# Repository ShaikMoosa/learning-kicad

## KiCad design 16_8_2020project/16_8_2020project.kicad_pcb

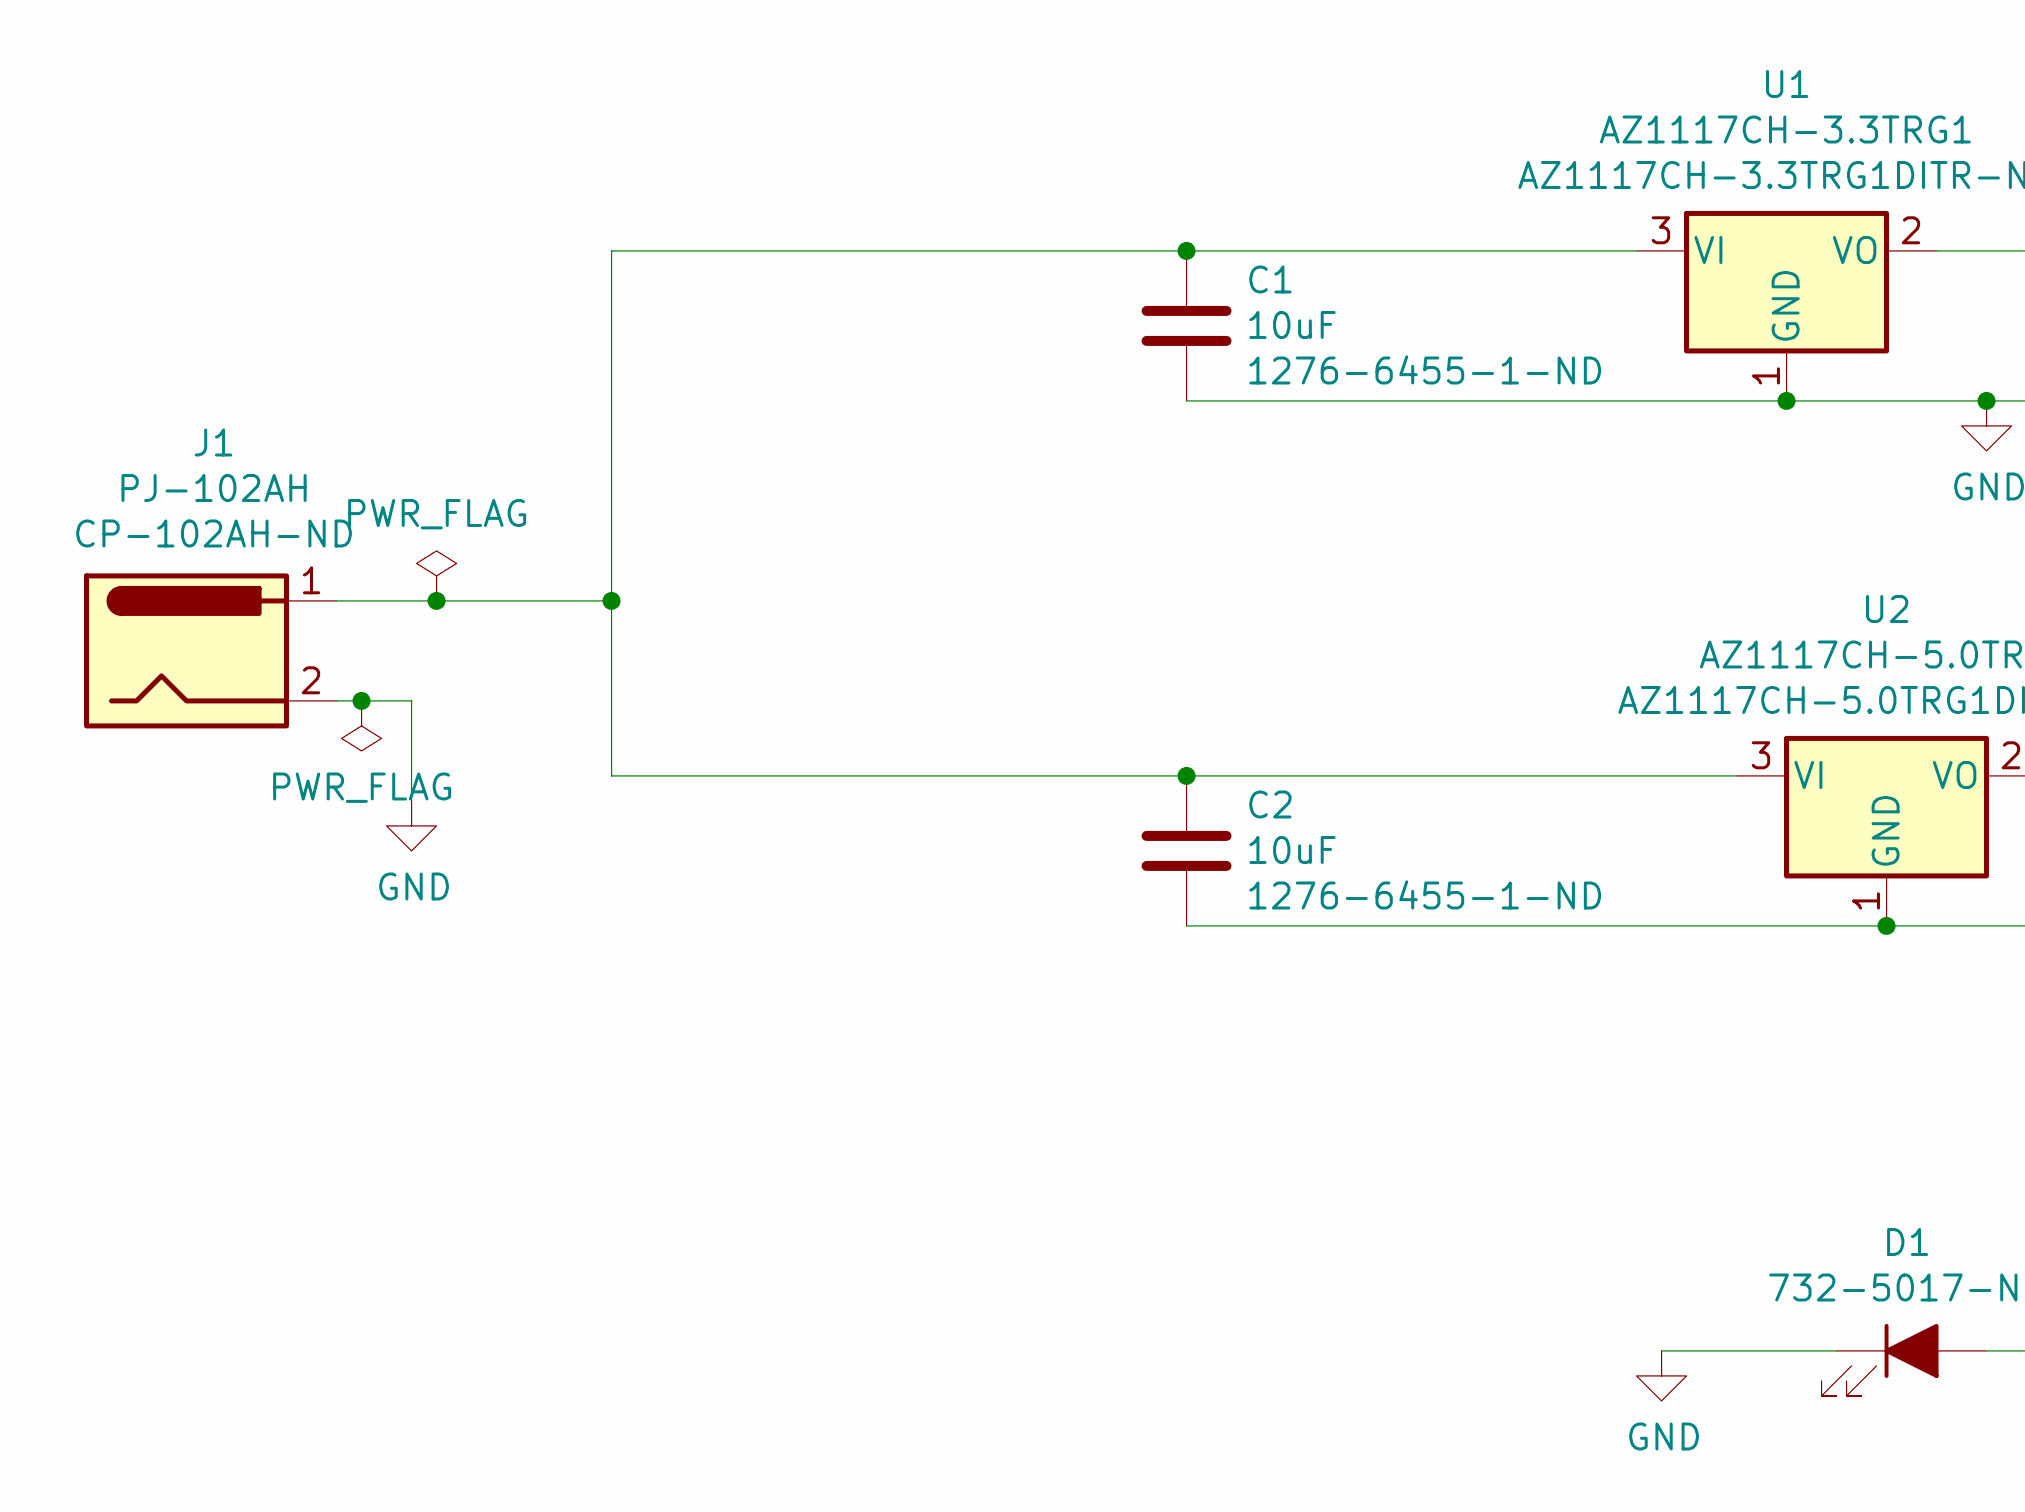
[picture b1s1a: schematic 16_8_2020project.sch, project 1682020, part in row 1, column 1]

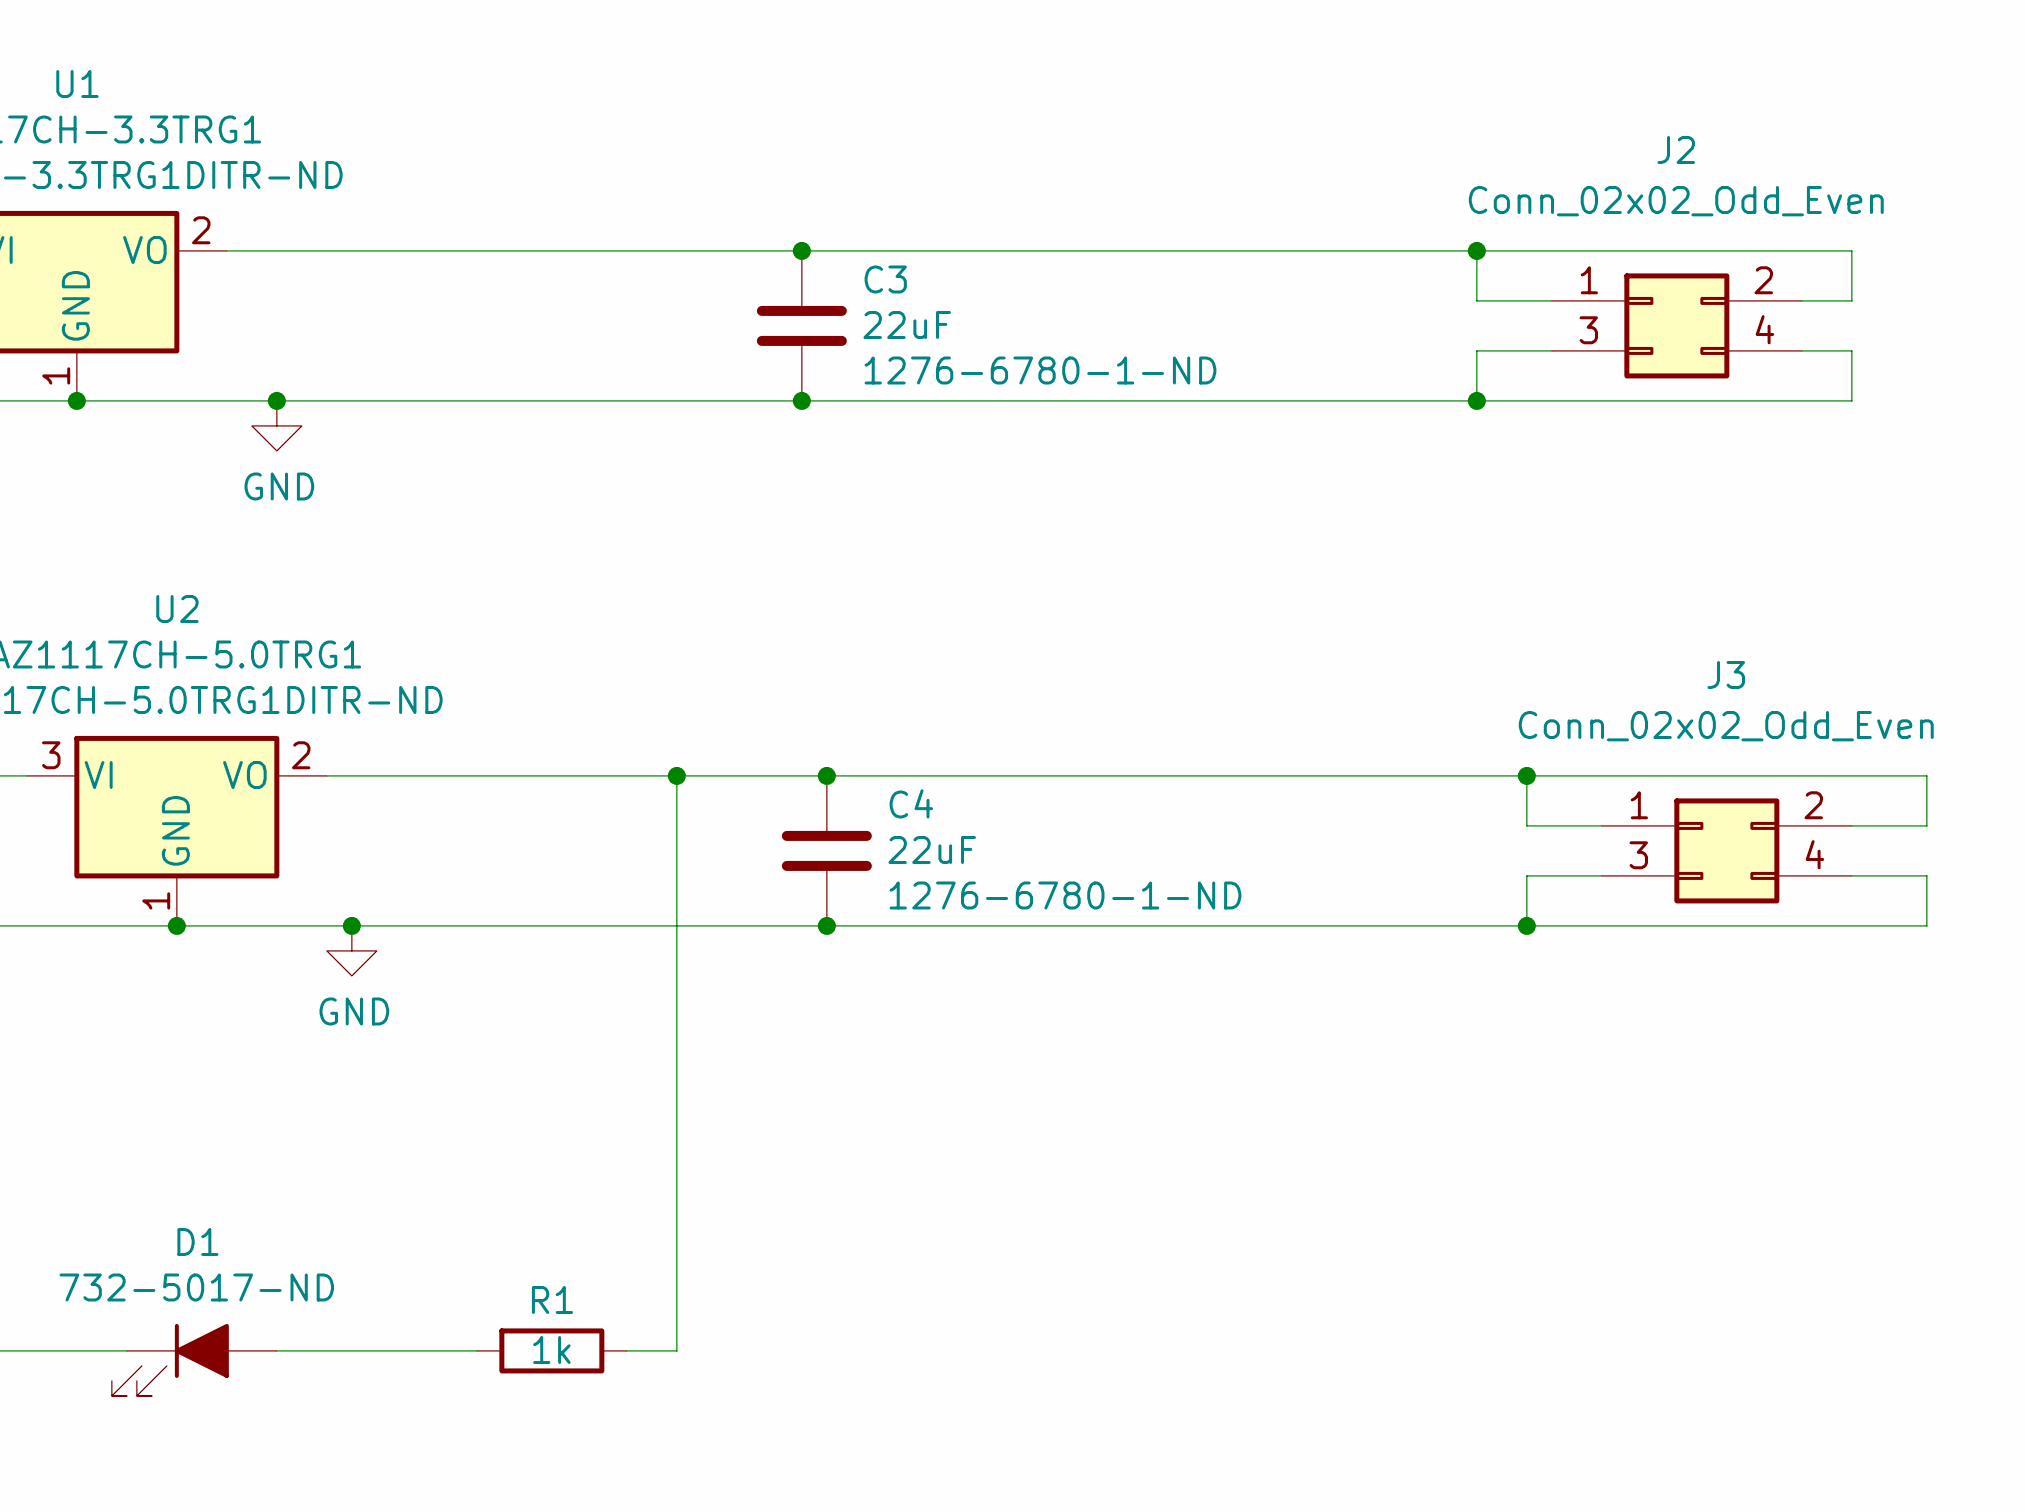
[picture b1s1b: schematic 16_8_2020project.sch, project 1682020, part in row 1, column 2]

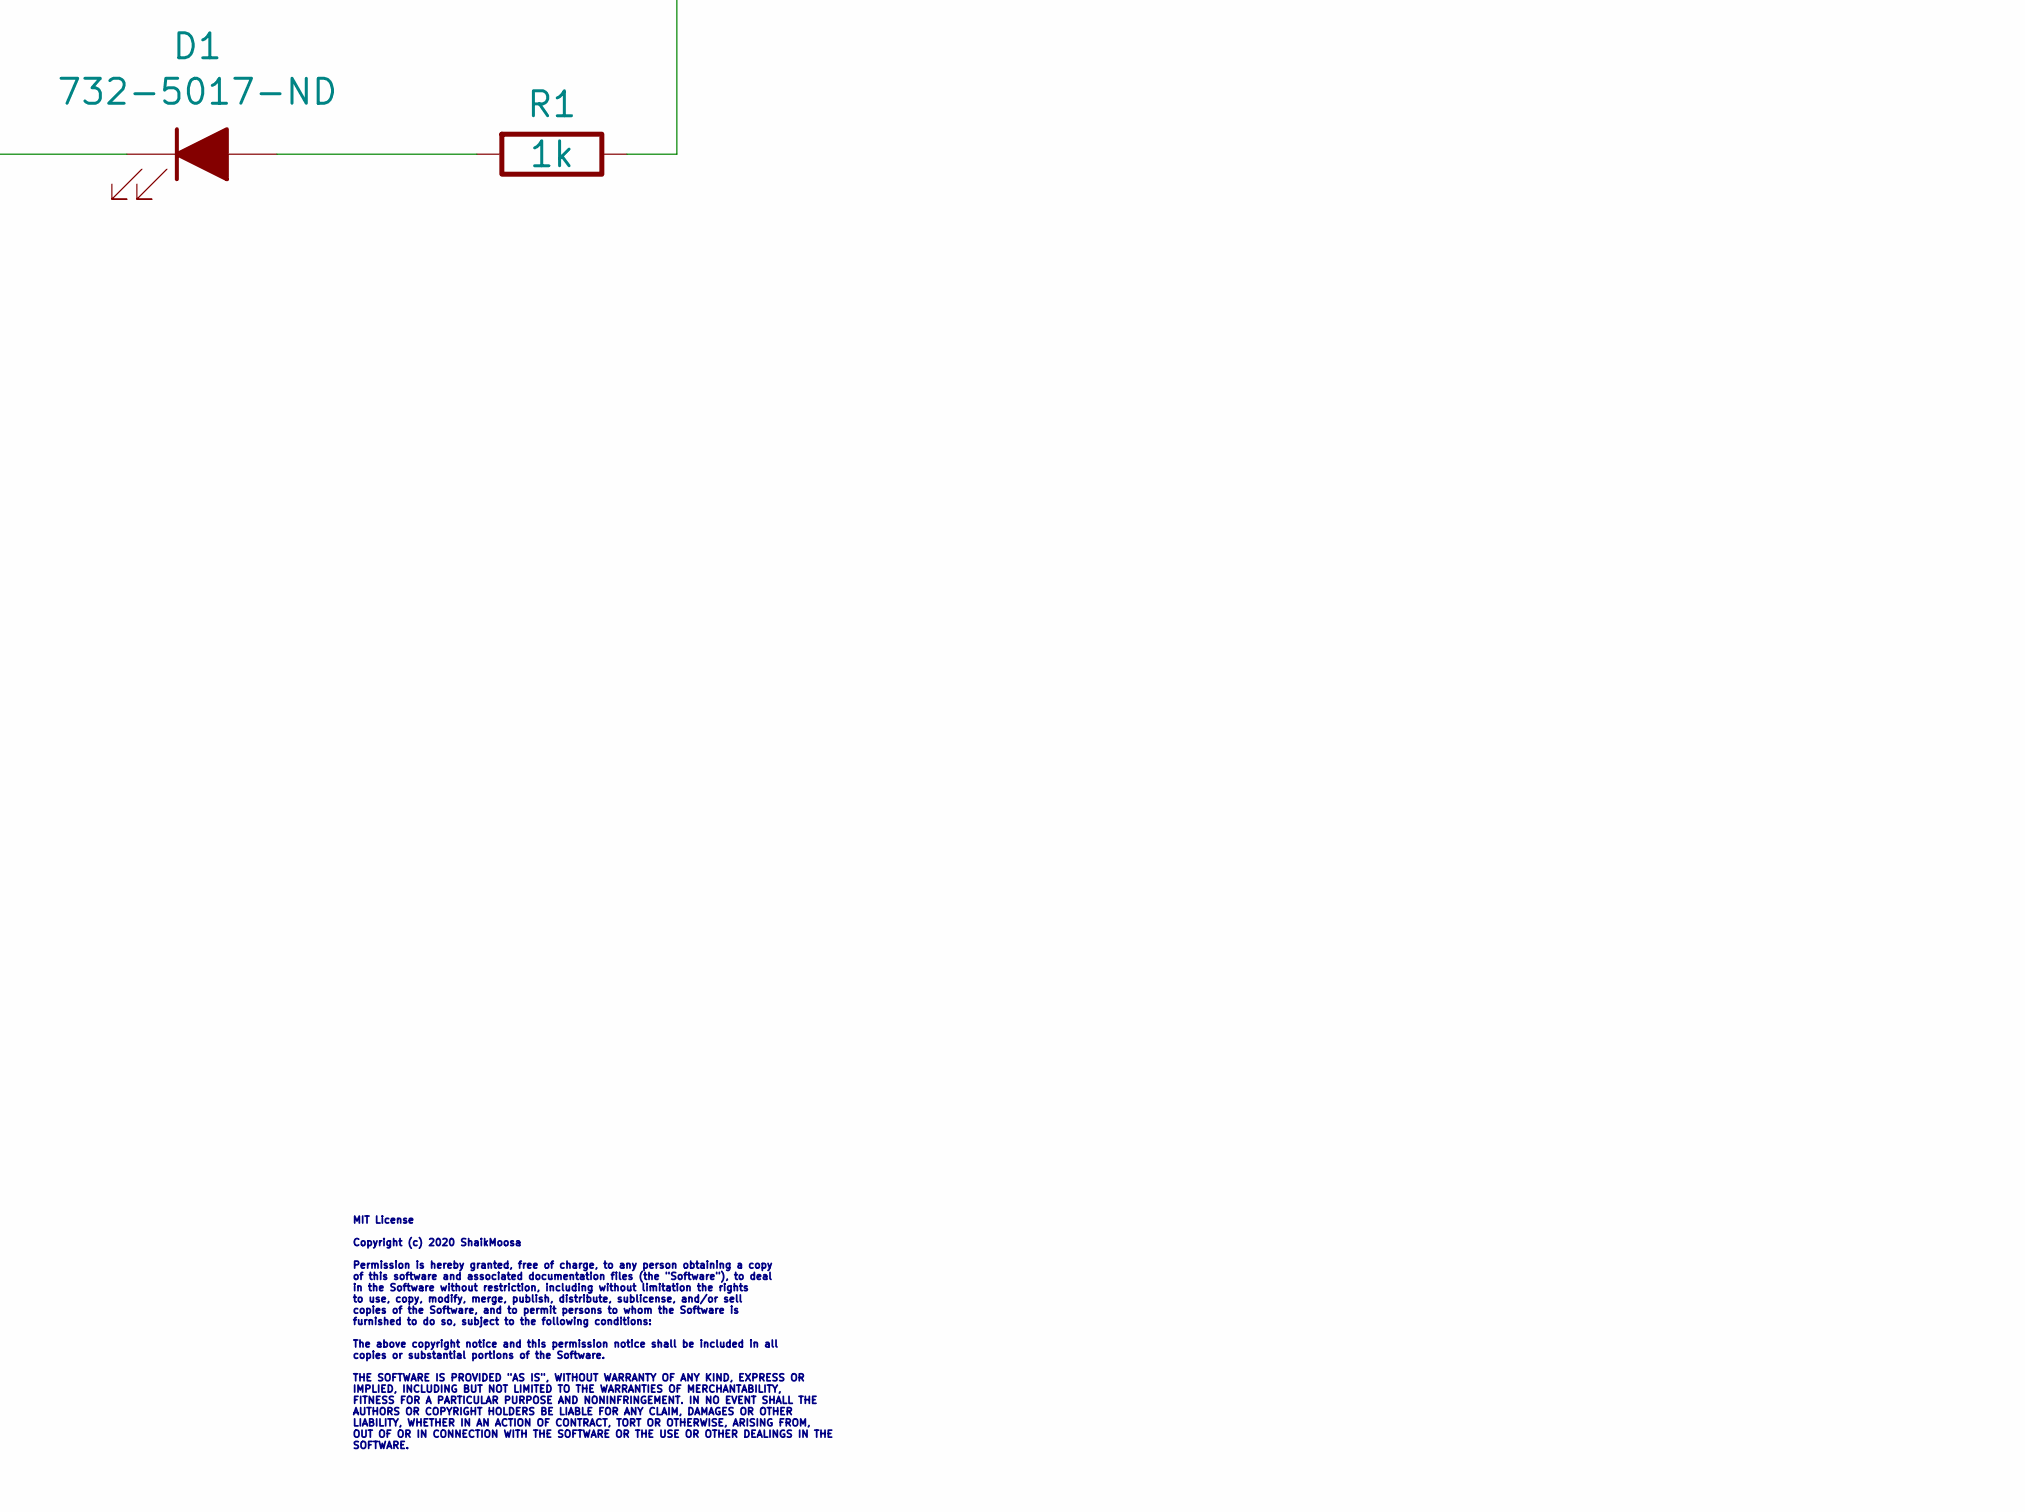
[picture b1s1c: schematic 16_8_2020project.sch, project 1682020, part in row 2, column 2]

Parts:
C1, C2: 10uF; C_0805_2012Metric_Pad1.15x1.40mm_HandSolder; digi key 1276-6455-1-ND
C3, C4: 22uF; C_0805_2012Metric_Pad1.15x1.40mm_HandSolder; digi key 1276-6780-1-ND
D1: LED_ALT; LED_D3.0mm; digi key 732-5017-ND
J1: PJ-102AH; BarrelJack_CUI_PJ-102AH_Horizontal; digi key CP-102AH-ND
J2, J3: Conn_02x02_Odd_Even; PinHeader_2x02_P2.54mm_Vertical
R1: 1k; R_0805_2012Metric_Pad1.15x1.40mm_HandSolder
U1: AZ1117CH-3.3TRG1; SOT-223-3_TabPin2; digi key AZ1117CH-3.3TRG1DITR-ND
U2: AZ1117CH-5.0TRG1; SOT-223-3_TabPin2; digi key AZ1117CH-5.0TRG1DITR-ND

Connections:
GND: C1.2, C2.2, C3.2, C4.2, D1.1 (K), J1.2, J2.3, J2.4, J3.3, J3.4, U1.1 (GND), U2.1 (GND)
unnamed: C1.1, C2.1, J1.1, U1.3 (VI), U2.3 (VI)
unnamed: C3.1, J2.1, J2.2, U1.2 (VO)
unnamed: C4.1, J3.1, J3.2, R1.1, U2.2 (VO)
unnamed: D1.2 (A), R1.2

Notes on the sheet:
MIT License Copyright (c) 2020 ShaikMoosa Permission is hereby granted, free of charge, to any person obtaining a copy of this software and associated documentation files (the "Software"), to deal in the Software without restriction, including without limitation the rights to use, copy, modify, mer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

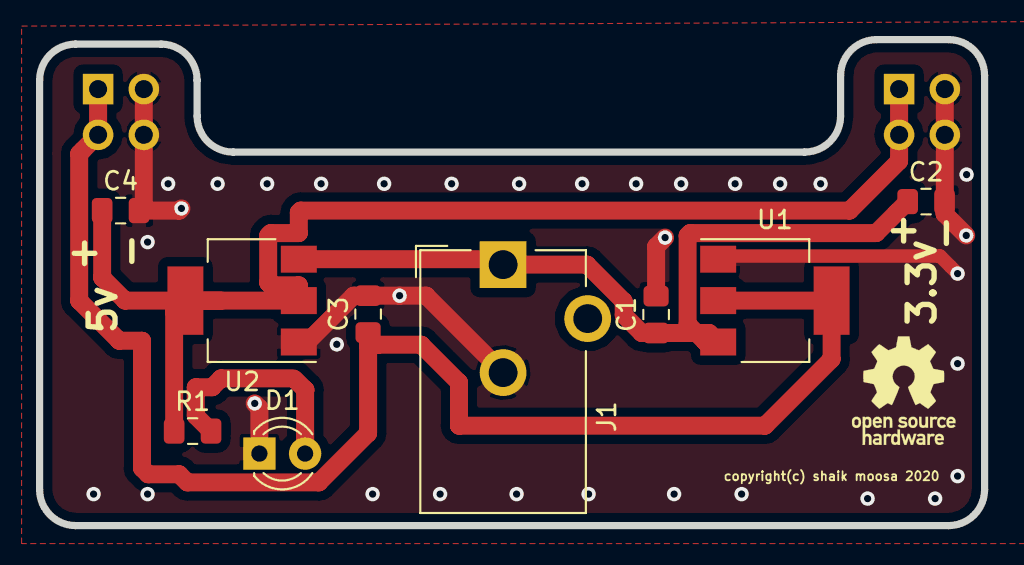
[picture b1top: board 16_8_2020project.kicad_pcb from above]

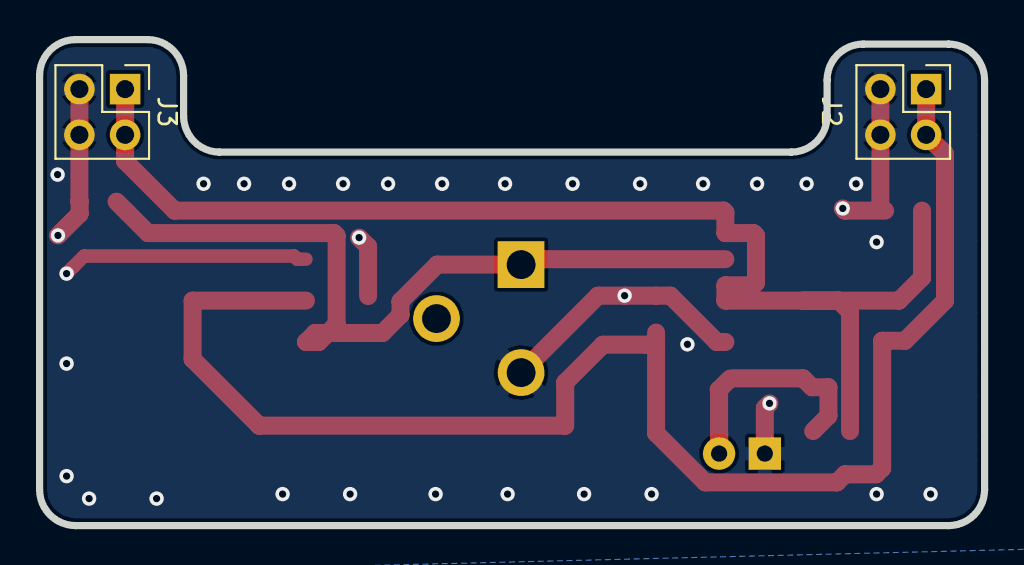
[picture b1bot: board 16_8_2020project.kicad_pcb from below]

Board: 2 copper layers, 52.5 x 27.0 mm, 11 parts (2 on the bottom side), 5 nets.

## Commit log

2020-08-21 Add files via upload
    first version pcb
2020-08-22 Add files via upload
    build 2

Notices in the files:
16_8_2020project/16_8_2020project.kicad_pcb:
copyright(c) shaik moosa 2020
